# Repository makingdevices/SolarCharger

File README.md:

<!-- Improved compatibility of back to top link: See: https://github.com/othneildrew/Best-README-Template/pull/73 -->

<!--
*** Thanks for checking out the Best-README-Template. If you have a suggestion
*** that would make this better, please fork the repo and create a pull request
*** or simply open an issue with the tag "enhancement".
*** Don't forget to give the project a star!
*** Thanks again! Now go create something AMAZING! :D
-->

<!-- PROJECT SHIELDS -->
<!--
*** I'm using markdown "reference style" links for readability.
*** Reference links are enclosed in brackets [ ] instead of parentheses ( ).
*** See the bottom of this document for the declaration of the reference variables
*** for contributors-url, forks-url, etc. This is an optional, concise syntax you may use.
*** https://www.markdownguide.org/basic-syntax/#reference-style-links
-->
[![Instagram][ig-shield]][ig-url]
[![PCBWAY][sponsor-shield]][sponsor-url]
[![Stargazers][stars-shield]][stars-url]
[![Issues][issues-shield]][issues-url]
[![LinkedIn][linkedin-shield]][linkedin-url]

<!-- PROJECT LOGO -->
<br />
<div align="center">

<h3 align="center">Making Devices</h3>

  <p align="center">
    Open Source projects where we struggle with engineering, electronics, coding and who knows what else... The solar charger uses the energy from a solar panel (using MPPT) to charge a Li-Ion rechargeable battery and provide an stable 5V - 0.6A output.
  </p>
</div>

<!-- TABLE OF CONTENTS -->
<details>
  <summary>Table of Contents</summary>
  <ol>
    <li>
      <a href="#about-the-project">About The Project</a>
      <ul>
        <li><a href="#built-with">Built With</a></li>
      </ul>
    </li>
    <li>
      <a href="#Build-one">Build one</a>
      <ul>
      </ul>
    </li>
    <li><a href="#usage">Usage</a></li>
    <li><a href="#roadmap">Roadmap</a></li>
    <li><a href="#license">License</a></li>
    <li><a href="#contact">Contact</a></li>
    <li><a href="#Sponsor">Sponsor</a></li>
  </ol>
</details>

<!-- ABOUT THE PROJECT -->
## About The Project

[![Bytes Counter Shot][product-screenshot]](https://github.com/makingdevices/SolarCharger)

The solar charger uses the energy from a solar panel (using MPPT) to charge a Li-Ion rechargeable battery and provide an stable 5V - 0.6A output. The project was created to test a small circuit before using it with other projects. 

<p align="right">(<a href="#readme-top">back to top</a>)</p>

### Built With

[![Kicad][kicad-shield]][kicad-url]
[![SPONSOR][sponsor-icon]][sponsor-url]

<p align="right">(<a href="#readme-top">back to top</a>)</p>

<!-- GETTING STARTED -->

## Build one
Documentation is updated.

1. Get the gerber files for the latest version: [V1.0](https://github.com/makingdevices/SolarCharger/blob/main/Gerber/SolarCharger_v1.zip) 
2. Send them to a PCB manufacturer ([Our Sponsor is PCBWAY][sponsor-url])
3. You should solder all the components in the board. ([The schematic is available here v1.0][schematic-url])

<p align="right">(<a href="#readme-top">back to top</a>)</p>

<!-- USAGE EXAMPLES -->
## Usage

As soon as you connect a battery, the output voltage will be activated. 

Protections:

- Solar Panel
  - Input voltage from 3V to 20V. It has over-voltage protection (OVP).
  - NTC Sensor: The charging process is compatible with the JEITA temperature standard for Li-Ion batteries, limiting the charge of the battery depending of the temperature of it.
  - Protection for short-circuit in the battery.

- Battery
  - Overcharge Detection Voltage at 4.2V (25mV accuracy)
  - Overcharge Hysteresis Voltage Range. (Release at 4.1V)
  - Overdischarge Detection Voltage at 2.5V.
  - Overdischarge Hysteresis Voltage Range. (Release at 3.0V)
  - Discharge overcurrent detection voltage. 
  - Short current detection voltage.    
  Note: You may want to select a different AP9214 configuration depending of your battery type. We have tested the AP9214L-AE-HSB.

- Output
  - Voltage fixed at 5V +-1.5%
  - Undervoltage protection. 
  - Overvoltage protection at 5.7V
  - Overcurrent and shortcircuit protection (+1A). It will recuperate when the shortcircuit is released. 

<p align="right">(<a href="#readme-top">back to top</a>)</p>

<!-- ROADMAP -->
## Roadmap

- [x] Assembly New Board
- [x] Test with electronic Load.
- [x] Validate ratings

See the [open issues](https://github.com/makingdevices/SolarCharger/issues) for a full list of proposed features (and known issues).

State: Project <b>FINISHED</b> - 12/09/2023

Priority: <b>High</b>

<p align="right">(<a href="#readme-top">back to top</a>)</p>

<!-- LICENSE -->
## License

Distributed under three licenses:
- [Hardware](/License/HW_cern_ohl_s_v2.pdf)
- [Software](/License/SW_GPLv3.0.txt)
- [Documentation](/License/Documentation_CC-BY-SA-4.0.txt)

[![GPL v3 License][license-shield]][license-url] 
<p align="right">(<a href="#readme-top">back to top</a>)</p>

<!-- CONTACT -->
## Contact

Making Devices - [@MakingDevices](https://www.instagram.com/makingdevices/)

Project Link: [https://github.com/makingdevices/SolarCharger](https://github.com/makingdevices/SolarCharger/)

Other Links: [LinkTree](https://makingdevices.com/links/)

<p align="right">(<a href="#readme-top">back to top</a>)</p>

<!-- Sponsor -->
## Sponsor

[PCBWAY](https://www.pcbway.com/?from=makingdevices) is the most professional PCB manufacturer for prototyping and low-volume production to work with in the world. With more than a decade in the field, They are committed to meeting the needs of their customers from different industries in terms of quality, delivery, cost-effectiveness and any other demanding requests. As Sponsor of Making Devices, they will be in charge of all the PCBs for MDV, allowing both of us to grow together in a long term partnership. We hope you take them into account for your both personal and professional prototypes or products.

[![Sponsor Shot][sponsor-screenshot]][sponsor-url]

<!-- MARKDOWN LINKS & IMAGES -->
<!-- https://www.markdownguide.org/basic-syntax/#reference-style-links -->
[contributors-shield]: https://img.shields.io/github/contributors/makingdevices/SolarCharger.svg?style=for-the-badge
[contributors-url]: https://github.com/makingdevices/SolarCharger/graphs/contributors
[forks-shield]: https://img.shields.io/github/forks/makingdevices/SolarCharger.svg?style=for-the-badge
[forks-url]: https://github.com/makingdevices/SolarCharger/network/members
[stars-shield]: https://img.shields.io/github/stars/makingdevices/SolarCharger.svg?style=for-the-badge
[stars-url]: https://github.com/makingdevices/SolarCharger/stargazers
[issues-shield]: https://img.shields.io/github/issues/makingdevices/SolarCharger.svg?style=for-the-badge
[issues-url]: https://github.com/makingdevices/SolarCharger/issues
[license-shield]: /images/license.png
[license-url]: https://github.com/makingdevices/SolarCharger/tree/main/License
[linkedin-shield]: https://img.shields.io/badge/-LinkedIn-black.svg?style=for-the-badge&logo=linkedin&colorB=555
[linkedin-url]: https://www.linkedin.com/company/making-devices/
[sponsor-shield]: https://img.shields.io/badge/SPONSOR-PCBWAY-black.svg?style=for-the-badge&colorB=1200
[sponsor-url]: https://www.pcbway.com/?from=makingdevices
[sponsor-screenshot]: /images/PCB_sponsor.png
[product-screenshot]: images/screenshotV1.jpg
[PIC]: https://img.shields.io/badge/PIC18LF45K50-000000?style=for-the-badge
[PIC-url]: http://ww1.microchip.com/downloads/en/devicedoc/40001350f.pdf
[kicad-shield]: https://img.shields.io/badge/kicad-0b03fc?style=for-the-badge&logo=kicad&logoColor=white
[kicad-url]: https://www.kicad.org/
[YT-screenshot]: images/YT_assembly.PNG
[sponsor-icon]:  https://img.shields.io/badge/-PCBWAY-black.svg?style=for-the-badge&colorB=1200
[ig-shield]: https://img.shields.io/badge/instagram-a83297?style=for-the-badge&logo=instagram&logoColor=white
[ig-url]: https://www.instagram.com/makingdevices/
[MPLAB-C]: https://img.shields.io/badge/MPLAB%20C18-DD0031?style=for-the-badge&logo=C&logoColor=white
[MPLAB-C-url]: https://www.microchip.com/en-us/development-tool/SW006011
[Svelte.dev]: https://img.shields.io/badge/Svelte-4A4A55?style=for-the-badge&logo=svelte&logoColor=FF3E00
[Svelte-url]: https://svelte.dev/
[Laravel.com]: https://img.shields.io/badge/Laravel-FF2D20?style=for-the-badge&logo=laravel&logoColor=white
[Laravel-url]: https://laravel.com
[Bootstrap.com]: https://img.shields.io/badge/Bootstrap-563D7C?style=for-the-badge&logo=bootstrap&logoColor=white
[Bootstrap-url]: https://getbootstrap.com
[JQuery.com]: https://img.shields.io/badge/jQuery-0769AD?style=for-the-badge&logo=jquery&logoColor=white
[JQuery-url]: https://jquery.com 
[schematic-url]: /Output_PDF/schematic_V1.pdf

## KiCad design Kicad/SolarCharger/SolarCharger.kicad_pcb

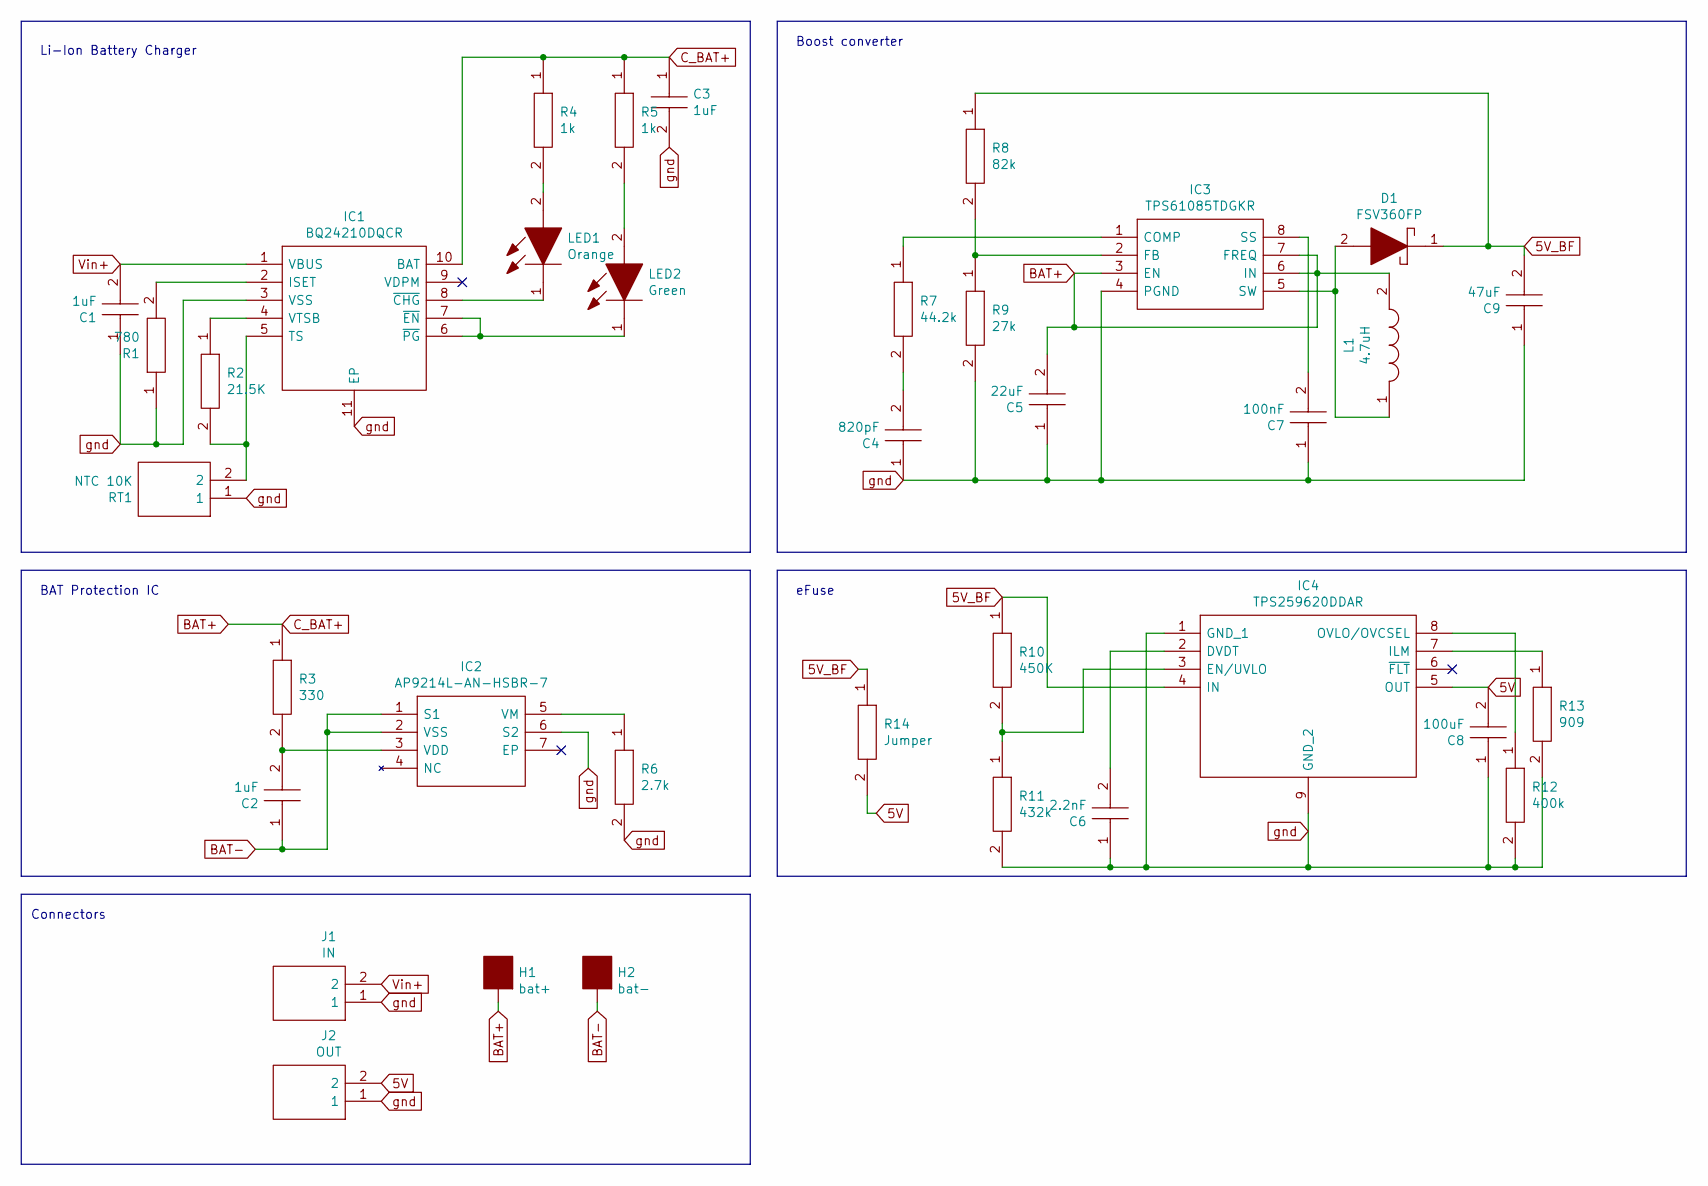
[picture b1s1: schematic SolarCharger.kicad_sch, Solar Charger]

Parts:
C1, C2, C3: 1uF; CAPC2012X140N; Manufacturer_Part_Number C0805C475M8RACTU
C4: 820pF; CAPC2012X140N; Manufacturer_Part_Number C0805C475M8RACTU
C5: 22uF; CAPC2012X140N; Manufacturer_Part_Number C0805C475M8RACTU
C6: 2.2nF; CAPC2012X140N; Manufacturer_Part_Number C0805C475M8RACTU
C7: 100nF; CAPC2012X140N; Manufacturer_Part_Number C0805C475M8RACTU
C8: 100uF; CAPC2012X140N; Manufacturer_Part_Number C0805C475M8RACTU
C9: 47uF; CAPC2012X140N; Manufacturer_Part_Number C0805C475M8RACTU
D1: FSV360FP; SS12FP; Mouser Part Number 512-FSV360FP
H1: bat+; mountinghole_battery
H2: bat-; mountinghole_battery
IC1: BQ24210DQCR; SON50P200X300X80-11N; Mouser Part Number 595-BQ24210DQCR
IC2: AP9214L-AN-HSBR-7; AP9214LANHSBR7; Mouser Part Number 621-AP9214L-AN-HSBR7
IC3: TPS61085TDGKR; SOP65P490X110-8N; Mouser Part Number 595-TPS61085TDGKR
IC4: TPS259620DDAR; SOIC127P600X170-9N; Mouser Part Number 595-TPS259620DDAR
J1: IN; 282834-2_1; Mouser Part Number 571-282834-2
J2: OUT; 282834-2_1; Mouser Part Number 571-282834-2
L1: 4.7uH; SRN6045_1; Mouser Part Number 652-SRN6045-4R7Y
LED1: Orange; LEDC2012X90N; Manufacturer_Part_Number SML-H12V8TT86
LED2: Green; LEDC2012X90N; Manufacturer_Part_Number SML-H12V8TT86
R1: 780; RESC2012X75N; Manufacturer_Part_Number ERJP6WF1303V
R2: 21.5K; RESC2012X75N; Manufacturer_Part_Number ERJP6WF1303V
R3: 330; RESC2012X75N; Manufacturer_Part_Number ERJP6WF1303V
R4, R5: 1k; RESC2012X75N; Manufacturer_Part_Number ERJP6WF1303V
R6: 2.7k; RESC2012X75N; Manufacturer_Part_Number ERJP6WF1303V
R7: 44.2k; RESC2012X75N; Manufacturer_Part_Number ERJP6WF1303V
R8: 82k; RESC2012X75N; Manufacturer_Part_Number ERJP6WF1303V
R9: 27k; RESC2012X75N; Manufacturer_Part_Number ERJP6WF1303V
R10: 450K; RESC2012X75N; Manufacturer_Part_Number ERJP6WF1303V
R11: 432k; RESC2012X75N; Manufacturer_Part_Number ERJP6WF1303V
R12: 400k; RESC2012X75N; Manufacturer_Part_Number ERJP6WF1303V
R13: 909; RESC2012X75N; Manufacturer_Part_Number ERJP6WF1303V
R14: Jumper; RESC2012X75N; Manufacturer_Part_Number ERJP6WF1303V
RT1: NTC 10K; THRMC2012X95N; Mouser Part Number 594-NTCS0805E3103GMT

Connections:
5V: C8.2, IC4.5 (OUT), J2.2, R14.2
5V_BF: C9.2, D1.1, IC4.4 (IN), R8.1, R10.1, R14.1
BAT+: C3.1, C5.2, H1.1, IC1.10 (BAT), IC3.3 (EN), IC3.6 (IN), IC3.7 (FREQ), L1.2, R3.1, R4.1, R5.1
BAT-: C2.1, H2.1, IC2.1 (S1), IC2.2 (VSS)
unnamed: C2.2, IC2.3 (VDD), R3.2
unnamed: C4.2, R7.2
unnamed: C6.2, IC4.2 (DVDT)
unnamed: C7.2, IC3.8 (SS)
unnamed: D1.2, IC3.5 (SW), L1.1
unnamed: IC1.2 (ISET), R1.2
unnamed: IC1.4 (VTSB), R2.1
unnamed: IC1.5 (TS), R2.2, RT1.2
unnamed: IC1.6 (~PG), IC1.7 (~EN), LED2.1
unnamed: IC1.8 (~CHG), LED1.1
unnamed: IC2.5 (VM), R6.1
unnamed: IC3.1 (COMP), R7.1
unnamed: IC3.2 (FB), R8.2, R9.1
unnamed: IC4.3 (EN/UVLO), R10.2, R11.1
unnamed: IC4.7 (ILM), R13.1
unnamed: IC4.8 (OVLO/OVCSEL), R12.1
unnamed: LED1.2, R4.2
unnamed: LED2.2, R5.2
Vin+: C1.2, IC1.1 (VBUS), J1.2
gnd: C1.1, C3.2, C4.1, C5.1, C6.1, C7.1, C8.1, C9.1, IC1.3 (VSS), IC1.11 (EP), IC2.6 (S2), IC3.4 (PGND), IC4.1 (GND_1), IC4.9 (GND_2), J1.1, J2.1, R1.1, R6.2, R9.2, R11.2, R12.2, R13.2, RT1.1

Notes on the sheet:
BAT Protection IC
Connectors
eFuse
Li-Ion Battery Charger
Boost converter

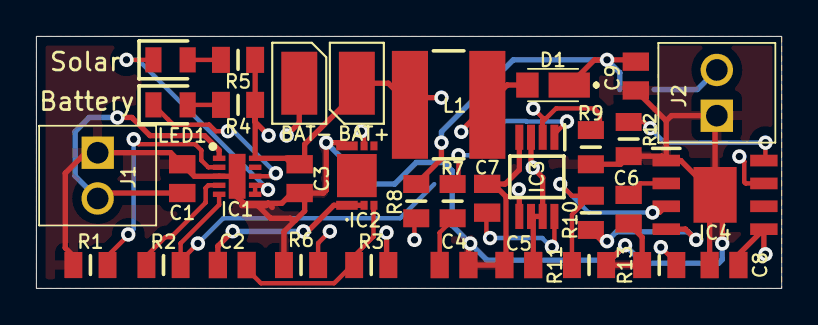
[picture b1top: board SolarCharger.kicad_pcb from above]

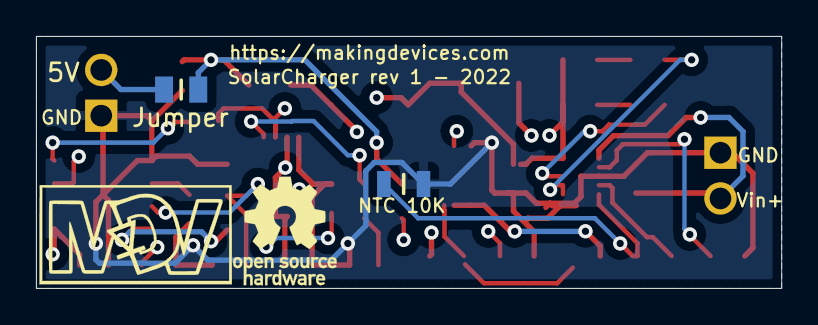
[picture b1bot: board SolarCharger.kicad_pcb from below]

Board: 4 copper layers, 41.4 x 14.0 mm, 36 parts (2 on the bottom side), 24 nets.

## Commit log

2023-01-08 Upload files
2023-04-20 no message
2023-09-12 Ignore backups from Kicad 7
2023-09-12 New version release
2023-09-12 New Readme
2023-09-12 New Readme v1
